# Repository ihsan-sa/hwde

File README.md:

# hwde

**An AI PCB engineer for KiCad and JLCPCB.** Printed circuit boards, designed
from a written brief.

This page is also a PDF with bigger pictures, the hwde showcase:
[hwde-showcase.pdf](docs/showcase/hwde-showcase.pdf). To install and run hwde,
see [Using hwde](docs/using-hwde.md).

You describe a board in plain words. hwde researches the parts, draws the
schematic, lays out and routes the board, checks it, and hands you the files a
factory needs to make it. A person reads the work and signs it off at each
stage before the next one starts.

*__lumina-carrier__ · 4 layers · 100 × 80 mm · 116 footprints · ordered,
fabricated. A carrier board for a stage-lighting fixture. hwde designed it, and
it was ordered from JLCPCB and made.*

## How a board is made

A board goes through five stages, and each stage ends with checks and a
person's sign-off.

*Figure 1. Each box is a stage, and each one writes a file the next one reads.*

A run starts from a brief, which can be a paragraph or a page. hwde first
researches the parts and picks an architecture, then chooses the real parts
and draws the schematic. Layout places the parts and routes the copper. The
checks run the electrical rules, the design rules and the circuit simulations,
and then the factory's own manufacturing rules on the exported Gerbers. What
comes out is the package: Gerbers, a bill of materials and a placement file
that JLCPCB can build and assemble from.

The work is split two ways. Subagents make the judgement calls, such as which
topology to use, how big a part must be, or whether a schematic is right, and
each one has a written contract that says what it may decide. Scripts do the
mechanical work, and they do it the same way every time. They drive KiCad, run
the routers and export the Gerbers. A script never makes a judgement, and an
agent never edits a board file by hand. Everything either of them makes is a
file in the board's own folder, so you can read it without hwde.

### What happens at the end of each stage

*Figure 2. A failed check or a refused sign-off goes to the fix loop, which
reworks the file and sends it round again.*

The checks that run depend on the stage, and each one writes its own report. A
pass only proves the checks that actually ran, which is why the reports are
kept one per check and not folded into a single verdict. When a check fails,
the fix loop reworks the file the stage made and the checks run again. When
they pass, a person still has to read the work and agree before the next stage
starts.

Every run also writes down what went wrong and why, with a date and a tag. The
next board reads those notes before it starts, so a mistake that cost one
board some time is not paid for again on the next.

## After the package

Three things can follow a finished package. A person can order the board,
/fwe can write its firmware, and /npie can plan how to bring it up.

*Figure 3. An order needs a person. Firmware and the bring-up plan have so far
run only in simulation.*

Ordering is deliberately hard to do by accident. JLCPCB has no public API for
its manufacturability review, so a person does that step in a browser. One
code path can place an order, and it takes 2-layer boards only. It refuses a
board whose files already record an order, and it will not run without a fresh
quote and a design that matches the one quoted. A person then has to type a
confirmation that names the board, the quantity and the total.

/fwe and /npie are two newer skills that take over where hwde stops. They
live in their own repositories, [ihsan-sa/fwe](https://github.com/ihsan-sa/fwe)
and [ihsan-sa/npie](https://github.com/ihsan-sa/npie). /fwe
writes firmware for a board, working from the board's own netlist to get the
pin map. /npie reads the same design and writes a staged bring-up procedure,
with pass and fail limits taken from the design, then runs it through one
driver layer that talks either to real instruments or to a simulated bench. So
far both have worked on one board, [the motor driver](#the-motor-driver), and
neither has touched hardware. The firmware builds, its unit tests pass on the
host, and it runs in the Renode emulator. The bring-up procedure has been run
once, against the simulated bench.

<!-- gallery:start - generated by docs/showcase/gallery.py from gallery.yaml and the boards repo; edit those, not this -->
## The boards

Twenty-three boards have reached a routed layout. They run from a linear
regulator with five parts to a three-phase motor driver.

| Board | What it is | Layers | Size (mm) | Where it stopped |
|---|---|--:|--:|---|
| stereo-class-d-amp | stereo class-D amplifier | 2 | 53.6 × 36.8 | made and measured, verification not passed |
| pd-trigger | USB-C PD bench trigger | 2 | 48 × 30 | ordered and made |
| lumina-carrier | lighting carrier, PoE-powered | 4 | 100 × 80 | ordered and made |
| rf-load-50ohm | 50 ohm / 200 W RF load at 13.56 MHz, fan-cooled, -40 dB tap | 2 | 60 × 60 | package ready |
| rp2040-mini | RP2040 dev board on the Pico footprint, USB-C | 2 | 21 × 51 | package ready |
| esp32c3-node | WiFi/BLE sensor node, LiPo | 2 | 26 × 38 | verification, findings open |
| lipo-boost | LiPo charger and 5 V boost | 2 | 53.9 × 38.8 | package ready |
| nfc-card | NFC business card | 2 | 88.9 × 50.8 | package ready |
| bldc-motor-driver | three-phase motor driver | 4 | 78 × 78 | package ready |
| pd-trigger-lite | small USB-C PD trigger | 2 | 25 × 15 | package ready |
| pd-trigger-lite-dip | the same, set by DIP switch | 2 | 25 × 21 | package ready |
| g0-sense | USB-C sensor node | 2 | 35.8 × 28.3 | package ready |
| bb-adc | single-channel ADC | 2 | 54.8 × 34.9 | package ready |
| bb-mcu | bare microcontroller board | 2 | 34.8 × 22.3 | package ready |
| bb-ldo | bare linear regulator | 2 | 34.7 × 34.7 | package ready |
| bb-amp | sensor amplifier chain | 2 | 48 × 28.3 | package ready |
| bb-buck | bare buck converter | 2 | 35 × 25 | package ready |
| rf-term-150w | 150 W RF dummy load head | 2 | 26 × 20 | package ready |
| rf-de-20m | 20 MHz Class E GaN stage | 4 | 120 × 80 | routing, findings open |
| sbuck-5v3a | 5 V / 3 A synchronous buck | 4 | 50 × 40 | package ready |
| usb-buck | USB device dev board | 4 | 50 × 40 | package ready |
| lumina-par | RGBW PAR daughter board | 4 | 100 × 80 | manufacturability, findings open |
| stm32-blinky | minimal STM32 dev board | 2 | 50 × 40 | package ready |

“Where it stopped” is the last stage the board reached, and it does not mean
the board is fit to release. Three boards were ordered from JLCPCB and made.
“Made and measured” means the board was also tested on a bench. “Package ready”
means every recorded check passed and the manufacturing package is built.
“Findings open” means a check failed and a person has yet to rule on it. Each
size is the bounding box of the board outline, and not every outline is a
rectangle.

### New boards

These boards were added after the rest of this chapter was written, so each
description is taken from the board's own requirements.

| | |
|---|---|
|  |  |
| __rf-load-50ohm__ · 2 layers · 60 × 60 mm · 21 footprints · package ready. A 50 ohm resistive RF load (dummy load) for 200 W continuous wave at 13.56 MHz, usable 1-30 MHz, for the owner's RF test system (it terminates the PCB-0023-A GaN inverter). | __rp2040-mini__ · 2 layers · 21 × 51 mm · 54 footprints · package ready. A general-purpose RP2040 microcontroller board that is a drop-in for the Raspberry Pi Pico (Raspberry Pi Ltd, 2021): same 21 x 51 mm outline, same 40-pin through-hole edge (as built: plain PTH, not castellated) with the Pico's pinout, same 3-pin SWD header position class (bottom edge, opposite USB). |

### The motor driver

*__bldc-motor-driver__ · 4 layers · 78 × 78 mm · 175 footprints · package
ready. A three-phase driver for brushless motors, running from 10 to 28 V. Six
N-channel MOSFETs make three half-bridges, a DRV8300 drives their gates, and an
STM32G431 runs the motor control. Each low-side leg has a 3 mΩ shunt read by an
INA240 current amplifier. The brief was a general spec and one frame of a video
showing someone else's demo board, so hwde wrote down every gap it had to fill
as a numbered assumption.*

The FETs are rated 60 V although the board runs at 28 V at most. The input TVS
diode clamps a surge at about 45 V, and every part on the motor supply is
chosen to survive that clamp, not just the working voltage. There is no fuse on
the board, and the notes call for a 20 A slow fuse in the supply lead.

*__bldc-motor-driver, top copper__ · F.Cu with net names. The three
half-bridges sit along the bottom edge, with phase A, B and C left to right,
each with its current amplifier below it. The board passes its checks with 390
written waivers, and the board's notes ask you to read them before you trust
it. Most cover stitching vias and the thin Kelvin and gate-return taps, which
the current-capacity check counts as power copper.*

This is the one board that /fwe and /npie have worked on. /fwe wrote the first
stage of its firmware, which spins the motor with six-step commutation. It
builds with warnings treated as errors, its unit tests pass on the host, and it
runs on an emulated STM32G431 in Renode. /npie wrote a bring-up procedure for
the board and ran it once against a simulated bench, where it passed. Neither
result says anything about real hardware, because the board has not been made.

### The amplifier

*__stereo-class-d-amp__ · 2 layers · 53.6 × 36.8 mm · 44 footprints · made and
measured, verification not passed. A stereo class-D amplifier that runs from a
single 12 V supply and drives 4 to 8 Ω speakers. Each output has a 10 µH LC
filter. The brief asked hwde to reproduce a published reference design, so the
two can be compared.*

The brief named the TPA3116D2, but hwde used the TPA3118D2 instead. The 3116
only comes with its thermal pad on top, which needs a heatsink bolted on. The
3118 has the pad underneath and sheds its heat into the board, so hwde kept a
25 by 25 mm ground area clear around it on both layers. That area is why the
board is bigger than the 44 by 34 mm reference.

*__stereo-class-d-amp, top copper__ · F.Cu with net names. The amplifier sits
in the middle of a solid ground pour, with the left channel's filter below it
and the right channel's above. The input connector is on the left edge and the
speaker pads are on the right.*

Ten assembled boards were ordered from JLCPCB on 30 September 2026, and one was
wired up and measured on the bench on 13 October. From 12 V into 6 Ω speakers,
one channel gave 10.9 W at 0.37% THD, and at 4.1 W a channel the board
delivered about 90% of its supply power to the speakers. It was ordered before
its verification checks passed, with eight waivers unsigned, and nobody has yet
measured the chip's temperature under load.

### A card, a sensor node and a battery board

These three were designed unattended on the same morning. The owner told hwde
to decide for itself, so hwde signed off its own stages and wrote down each
call it made, with the reason.

*__nfc-card__ · 2 layers · 88.9 × 50.8 mm · 19 footprints · package ready. A
business card you tap with a phone. The phone reads a web address from the NFC
tag and opens it, and while the phone is near, the tag takes power from its
field and lights a pattern of LEDs. There is no battery and no microcontroller.
The antenna is a coil printed around the edge of a 0.8 mm board, thin enough to
carry in a wallet.*

| | |
|---|---|
|  |  |
| __esp32c3-node__ · 2 layers · 26 × 38 mm · 41 footprints · verification, findings open. A small WiFi and Bluetooth sensor node built around an ESP32-C3 module. USB-C powers it and also flashes it, through the chip's own USB, so there is no USB-serial bridge. It charges a single LiPo cell and keeps running with or without one, and a BME280 and a Qwiic connector share one I²C bus. | __lipo-boost__ · 2 layers · 53.9 × 38.8 mm · 33 footprints · package ready. It charges a single LiPo cell from USB and makes 5 V at 1 A on a USB-A socket from the cell. While USB is plugged in, the output keeps running from USB as the cell charges. The brief asked for a board in the class of the PowerBoost 1000C, designed from the datasheets rather than copied. |

### The small PD triggers

| | |
|---|---|
|  |  |
| __pd-trigger-lite__ · 2 layers · 25 × 15 mm · 15 footprints · package ready. Plug in a USB-C charger and the board asks it for 9, 12, 15 or 20 V, at up to 3 A, and passes it to two output holes. One solder link picks the voltage. hwde chose the CH224A over the CH224K the brief named, because its sense pin takes the bus voltage directly. That removes a dropper resistor, a sense resistor and the pull-ups. | __pd-trigger-lite-dip__ · 2 layers · 25 × 21 mm · 13 footprints · package ready. The same board with a five-way DIP switch instead of the solder links, which adds 5 V to the choices. You set exactly one switch before you plug it in. The board grew from 15 to 21 mm to make room for the switch. |

Both are smaller versions of pd-trigger, the bench tool that was ordered and
made.

### Ordered and fabricated

lumina-carrier, the board at the start, is the carrier for a stage-lighting
fixture. It takes power over Ethernet through a PD controller and a 100 V buck,
and it has an expansion connector that a fixture-specific daughter board plugs
into. The connector's pinout is frozen, because another board depends on it.
The amplifier was ordered too, and the third board that was ordered is a bench
tool.

*__pd-trigger__ · 2 layers · 48 × 30 mm · 30 footprints · ordered and made. A
USB-C Power Delivery sink asks a charger for 5, 9, 12, 15 or 20 V, and you pick
which on the board. The rail comes out on a screw terminal rated for 5 A. The
board converts nothing and just passes the rail through.*

### Power and RF

| | |
|---|---|
|  |  |
| __sbuck-5v3a__ · 4 layers · 50 × 40 mm · 44 footprints · package ready. A synchronous buck that takes 7–18 V in and holds 5.0 V ±2% at 3 A out. It is an open-frame power module. | __rf-term-150w__ · 2 layers · 26 × 20 mm · 6 footprints · package ready. A 50 Ω, 150 W dummy load head for DC to 25 MHz. The element bolts to a heatsink you supply, so the board is only the RF launch and the mounting. It looks almost bare because none of its six footprints has a 3D model, so the connector and the element are not drawn. |

*__rf-de-20m__ · 4 layers · 120 × 80 mm · 80 footprints · routing, findings
open. A 20 MHz Class E RF power stage that puts 200 W into 50 Ω from a 40 V
bus. A GaN gate driver buffers the PWM drive from an SMA input, and one eGaN
FET switches. A resonant tank and an L-match turn the 4.6 Ω load line into 50 Ω
at the output SMA. The owner fixed the topology and the two core parts after a
costed trade study, and hwde did the rest.*

### Lighting

*__lumina-par__ · 4 layers · 100 × 80 mm · 158 footprints · manufacturability,
findings open. The RGBW PAR daughter board that stacks on lumina-carrier. It
takes the carrier's frozen connector as given. Its power budget depends on the
power-over-Ethernet class the fixture is granted, so hwde worked it out again
here. The silkscreen warns that the board floats at the power-over-Ethernet
potential, because an earthed probe breaks the fixture's power negotiation.*

| | |
|---|---|
|  |  |
| __lumina-par, straight down__ · top-down view. The same board from straight above, so the routing shows. | __lumina-carrier, underneath__ · bottom view. Every part on the carrier is on the top side, so the back carries routing and vias and nothing else. |

### Microcontroller boards

*__g0-sense__ · 2 layers · 35.8 × 28.3 mm · 30 footprints · package ready. A
temperature and humidity node that runs off USB-C. An LDO makes 3.3 V from the
5 V supply, and an STM32G030 reads a Sensirion SHT4x over I²C. The same bus
comes out on a Qwiic connector, the readings go out on a UART header, and you
program it over SWD. hwde designed this one from end to end in a single
unattended run.*

| | |
|---|---|
|  |  |
| __usb-buck__ · 4 layers · 50 × 40 mm · 28 footprints · package ready. An STM32F103 board that talks USB at full speed. The Micro-B socket carries both power and data, and there is an LED, a button and an SWD header. | __stm32-blinky__ · 2 layers · 50 × 40 mm · 20 footprints · package ready. The simplest useful board here: an STM32F103, an 8 MHz crystal, one LED, an LDO and an SWD header. |

### Building blocks

These five boards each carry a single block and nothing else. They are meant to
be studied and measured on a bench, so they leave out protection, filtering,
indicators and spare rails on purpose.

| | |
|---|---|
|  |  |
| __bb-buck__ · 2 layers · 35 × 25 mm · 20 footprints · package ready. 18–30 V in and 5 V at 2 A out, on a screw terminal. It carries the converter and exactly what its datasheet requires. | __bb-ldo__ · 2 layers · 34.7 × 34.7 mm · 5 footprints · package ready. 5 V in and 3.3 V at 500 mA out. It stays in regulation in still air on the board's own copper. |
|  |  |
| __bb-mcu__ · 2 layers · 34.8 × 22.3 mm · 14 footprints · package ready. One MCU with a 3.3 V rail coming in, its debug header and four GPIO. There is no regulator and no second rail. | __bb-adc__ · 2 layers · 54.8 × 34.9 mm · 25 footprints · package ready. 0–5 V in on a screw terminal and 12 bits at up to 10 kSa/s out on a header. It gives up speed for DC accuracy. |
|  | |
| __bb-amp__ · 2 layers · 48 × 28.3 mm · 14 footprints · package ready. A 0–20 mV bridge signal in and 0–3.3 V out, from DC to 1 kHz. | |

Two more boards stopped before layout and have no PCB to show: lumina-strobe
(LUMINA strobe daughter board) and buck-5v3a (12 V to 5 V / 3 A synchronous
buck). They are in the boards repository at the stage they reached.
<!-- gallery:end -->

## What it can and cannot do yet

hwde is an engineering assistant. It does not release a board on its own, and
a person signs off at every stage.

**What holds**

- Every board in the table went from a written brief to a routed layout, among
  them a 4-layer 200 W RF stage and a 4-layer motor driver.
- The ones marked ordered were made by JLCPCB, and their files record the
  order numbers.
- Every check is a script, and the findings are kept per check rather than as
  a single verdict.
- Everything a run produces is a file in that board's folder, and you can read
  it without hwde.

**What does not**

- JLCPCB's manufacturability review has no public API, so a person still does
  that step in a browser.
- The electrical and thermal checks are engineering screens, and each states
  its own accuracy. None of them is a certification, and nothing here is
  certified for mains, medical, automotive or aerospace use.
- The firmware and the bring-up procedure have only run in simulation. The
  amplifier, which has no firmware, was measured on a real bench by hand, but
  no board has been brought up with them yet.

---

Board facts come from each board's own files in the boards repository
(`.kicad_pcb`, `state.json` and its notes), and the gallery above is
regenerated from them whenever a board is added or changed. How that works,
and how to rebuild the pictures and the PDF, is in
[docs/showcase](docs/showcase/README.md).

To install and run hwde, call it from another agent, or find which document
answers which question, see [Using hwde](docs/using-hwde.md).

## License

MIT - see [LICENSE](LICENSE). Vendor datasheets, component 3D models and
footprints pulled from LCSC/EasyEDA are third-party material, not under MIT -
see [NOTICE](NOTICE).

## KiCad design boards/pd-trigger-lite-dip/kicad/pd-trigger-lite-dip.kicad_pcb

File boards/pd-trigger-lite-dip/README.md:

# pd-trigger-lite-dip

A 25 x 21 mm, 2-layer USB-C PD trigger. Plug in a PD charger and it passes VBUS straight to two
2.54 mm output holes at 5, 9, 12, 15 or 20 V (3 A max). The voltage is picked with a 5-position
DIP switch: exactly one switch ON, set before plugging in. It is pd-trigger-lite with the solder
links replaced by the switch. Controller: WCH CH224A. Full owner guide, with the switch table:
`fab/pd-trigger-lite-dip-guide.pdf`.

| Switch ON (others OFF) | 1 | 2 | 3 | 4 | 5 |
|---|---|---|---|---|---|
| Output | 5 V | 9 V | 12 V | 15 V | 20 V |

## Files

| Path | What it is |
|---|---|
| `fab/pd-trigger-lite-dip-guide.pdf` | Owner guide: what it does, schematic, switch settings, BOM, cost, JLC ordering |
| `fab/pd-trigger-lite-dip_gerbers.zip` | Gerbers + drill for JLCPCB |
| `fab/BOM.csv` | JLC assembly BOM (Comment, Designator, Footprint, LCSC Part #) |
| `fab/CPL.csv` | JLC placement file (Designator, Mid X, Mid Y, Layer, Rotation) |
| `fab/prebuy.csv` | Extended parts you may need to pre-buy at JLC, with quantities for 5 boards |
| `fab/BOM-full.csv` | BOM of record incl. the unassembled output holes (J2) |
| `fab/quote.json` | Estimated JLC quote, qty 5 with assembly |
| `kicad/` | KiCad 10 project; the schematic is generated by `kicad/gen/root.py` |
| `reports/` | ERC/DRC/verify/DFM gate reports, schematic PDF, renders, guide source |
| `architecture/`, `requirements.md`, `log/` | Design decisions and the run journal |

## Estimated cost, 5 boards assembled at JLC (2026-09-24)

| Item | USD |
|---|---|
| PCB, 5 pcs, 2 layers, 25 x 21 mm, 1.6 mm, HASL | 2.00 |
| Economic PCBA setup | 8.00 |
| Stencil | 8.00 |
| Extended-part fees: CH224A, USB-C receptacle, DIP switch (3 x 3.00) | 9.00 |
| Solder joints (49 x 5 x 0.0017) | 0.42 |
| Parts, 5 boards (about 1.09 per board, LCSC unit prices; the switch is 0.53) | 5.44 |
| **Total before shipping** | **about 33** |

Assumptions: prices from the hwde price table (`reference/jlc_pricing.yaml`, verified 2026-07-24)
and LCSC unit prices pulled 2026-09-24. These are estimates: live JLC bare-PCB prices have run
1.9-3.1x above that table, so allow roughly 33-40 USD. Shipping is extra and region-dependent
(about 2-20 USD depending on carrier). The JLC cart is the only real quote. Nothing has been ordered.

## You may need to pre-buy these at JLC

JLC's BOM review may show an Extended part as idle stock: unselected, at quantity 0, until you buy
it into your JLC parts inventory. JLC's public parts search can't tell idle stock from stock that
assembles straight away, so every Extended part is listed. If one comes up unselected, buy it from
the BOM review page, then select it.

| LCSC | Part | Ref | Qty for 5 boards |
|---|---|---|---|
| C2798175 | USB-C receptacle 6P (TYPE-C-6M-001) | J1 | 5 |
| C7421518 | DIP switch 5P, 1.27 mm (1.27-5P TPPT) | SW1 | 5 |
| C42459160 | CH224A PD sink controller | U1 | 5 |

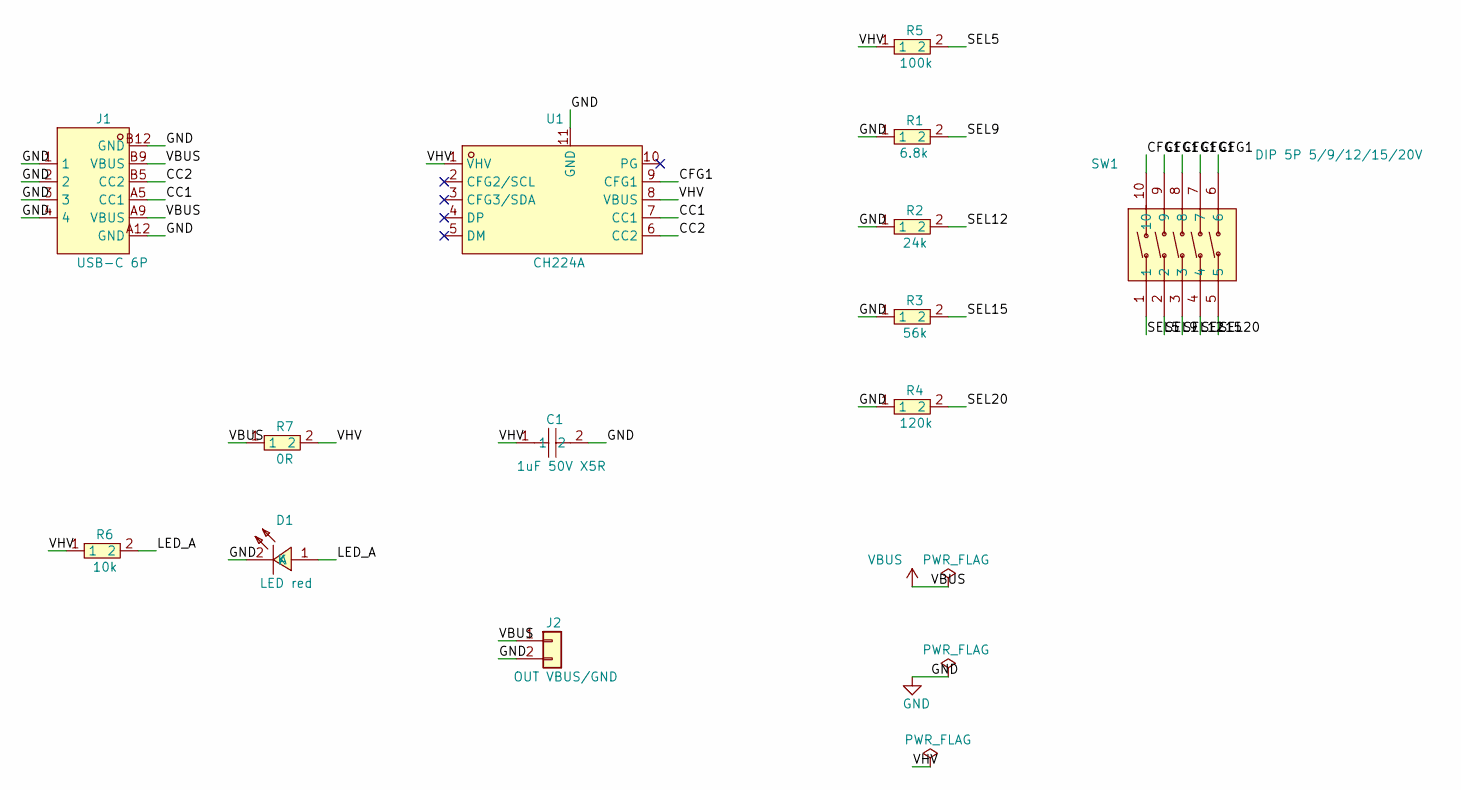
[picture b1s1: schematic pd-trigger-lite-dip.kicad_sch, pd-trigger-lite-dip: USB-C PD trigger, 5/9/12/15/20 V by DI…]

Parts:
C1: 1uF 50V X5R; C0603; LCSC C15849
D1: LED red; LED-SMD_L1.6-W0.8-R-RD; LCSC C2286
J1: USB-C 6P; USB-C-SMD_918-418K2023S40006; LCSC C2798175
J2: OUT VBUS/GND; OUT_2P_P2.54_D1.1
R1: 6.8k; R0603; LCSC C23212
R2: 24k; R0603; LCSC C23352
R3: 56k; R0603; LCSC C23206
R4: 120k; R0603; LCSC C25808
R5: 100k; R0603; LCSC C25803
R6: 10k; R0603; LCSC C25804
R7: 0R; R0603; LCSC C21189
SW1: DIP 5P 5/9/12/15/20V; SW-SMD_5P-P1.27_1.27-5P; LCSC C7421518
U1: CH224A; ESSOP-10_L4.9-W3.9-P1.0-LS6.0-TL-EP; LCSC C42459160

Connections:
/CC1: J1.A5 (CC1), U1.7 (CC1)
/CC2: J1.B5 (CC2), U1.6 (CC2)
/CFG1: SW1.6, SW1.7, SW1.8, SW1.9, SW1.10, U1.9 (CFG1)
/LED_A: D1.1 (A), R6.2
/SEL5: R5.2, SW1.1
/SEL9: R1.2, SW1.2
/SEL12: R2.2, SW1.3
/SEL15: R3.2, SW1.4
/SEL20: R4.2, SW1.5
/VHV: C1.1, R5.1, R6.1, R7.2, U1.1 (VHV), U1.8 (VBUS)
GND: C1.2, D1.2 (K), J1.1, J1.2, J1.3, J1.4, J1.A12 (GND), J1.B12 (GND), J2.2, R1.1, R2.1, R3.1, R4.1, U1.11 (GND)
VBUS: J1.A9 (VBUS), J1.B9 (VBUS), J2.1, R7.1

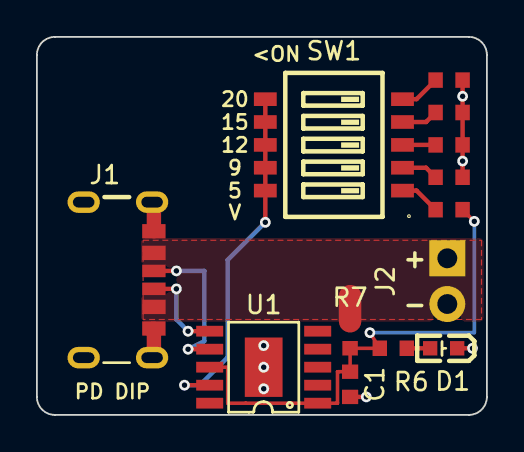
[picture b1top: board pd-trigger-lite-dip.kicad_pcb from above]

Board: 2 copper layers, 25.0 x 21.0 mm, 13 parts (0 on the bottom side), 12 nets.

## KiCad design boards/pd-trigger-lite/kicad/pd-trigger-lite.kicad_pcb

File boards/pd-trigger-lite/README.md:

# pd-trigger-lite

A 25 x 15 mm, 2-layer USB-C PD trigger. Plug in a PD charger and it passes VBUS straight to two
2.54 mm output holes at 9, 12, 15 or 20 V (3 A max). The voltage is set by one 0603 link; it ships
at 12 V. Controller: WCH CH224A in single-resistor mode. Full owner guide: `fab/pd-trigger-lite-guide.pdf`.

## Files

| Path | What it is |
|---|---|
| `fab/pd-trigger-lite-guide.pdf` | Owner guide: what it does, schematic, voltage setting, BOM, cost, JLC ordering |
| `fab/pd-trigger-lite_gerbers.zip` | Gerbers + drill for JLCPCB |
| `fab/BOM.csv` | JLC assembly BOM (Comment, Designator, Footprint, LCSC Part #) |
| `fab/CPL.csv` | JLC placement file (Designator, Mid X, Mid Y, Layer, Rotation) |
| `fab/BOM-full.csv` | BOM of record incl. the unassembled links (JP1-3) and output holes (J2) |
| `fab/quote.json` | Estimated JLC quote, qty 5 with assembly |
| `kicad/` | KiCad 10 project; the schematic is generated by `kicad/gen/root.py` |
| `reports/` | ERC/DRC/verify/DFM gate reports, schematic PDF, renders, reviews |
| `architecture/`, `requirements.md`, `log/` | Design decisions and the run journal |

## Estimated cost, 5 boards assembled at JLC (2026-09-24)

| Item | USD |
|---|---|
| PCB, 5 pcs, 2 layers, 25 x 15 mm, 1.6 mm, HASL | 2.00 |
| Economic PCBA setup | 8.00 |
| Stencil | 8.00 |
| Extended-part fees: CH224A, USB-C receptacle (2 x 3.00) | 6.00 |
| Solder joints (39 x 5 x 0.0017) | 0.33 |
| Parts, 5 boards (about 0.56 per board, LCSC unit prices) | 2.78 |
| **Total before shipping** | **about 27** |

Assumptions: prices from the hwde price table (`reference/jlc_pricing.yaml`, verified 2026-07-24)
and LCSC unit prices pulled 2026-09-24. These are estimates: live JLC bare-PCB prices have run
1.9-3.1x above that table, so allow roughly 27-35 USD. Shipping is extra and region-dependent
(about 2-20 USD depending on carrier). The JLC cart is the only real quote. Nothing has been ordered.

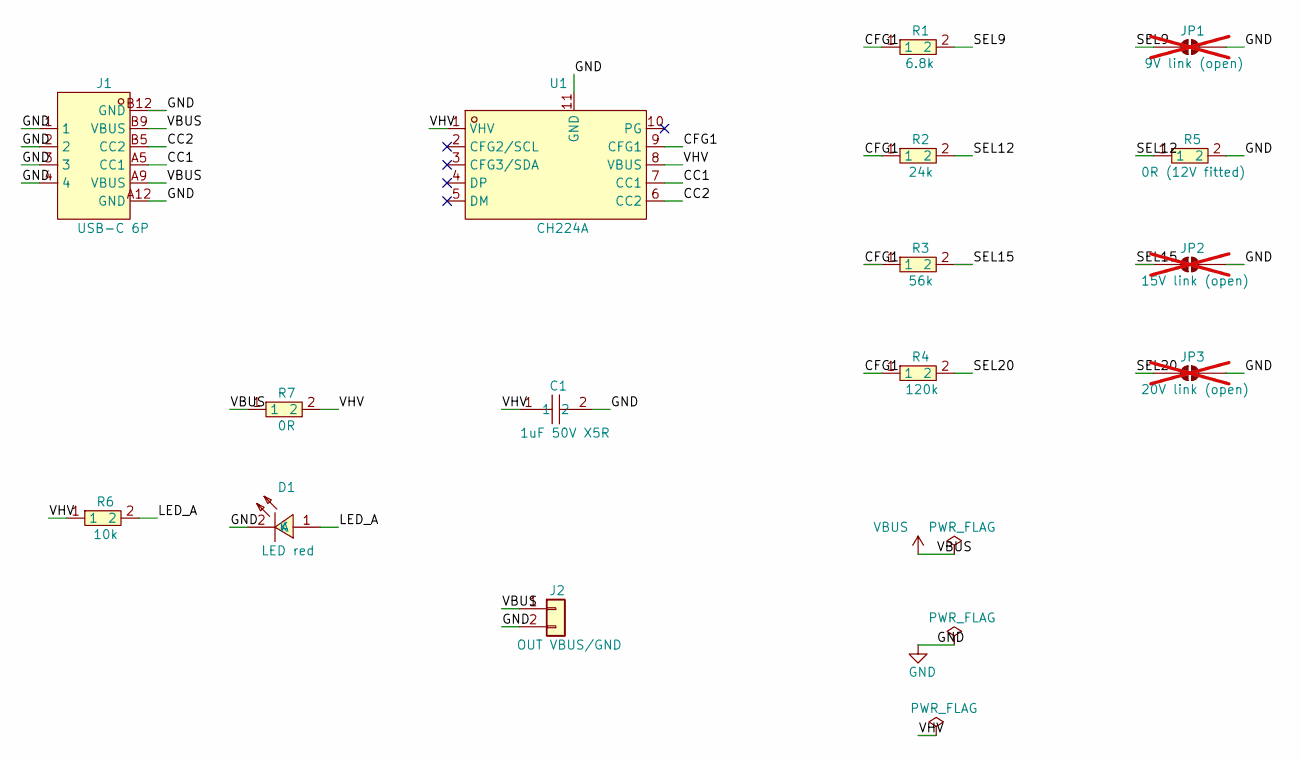
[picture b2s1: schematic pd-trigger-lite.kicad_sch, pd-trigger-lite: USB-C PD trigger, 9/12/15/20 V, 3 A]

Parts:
C1: 1uF 50V X5R; C0603; LCSC C15849
D1: LED red; LED-SMD_L1.6-W0.8-R-RD; LCSC C2286
J1: USB-C 6P; USB-C-SMD_918-418K2023S40006; LCSC C2798175
J2: OUT VBUS/GND; OUT_2P_P2.54_D1.1
JP1: 9V link (open); R0603; not fitted
JP2: 15V link (open); R0603; not fitted
JP3: 20V link (open); R0603; not fitted
R1: 6.8k; R0603; LCSC C23212
R2: 24k; R0603; LCSC C23352
R3: 56k; R0603; LCSC C23206
R4: 120k; R0603; LCSC C25808
R5: 0R (12V fitted); R0603; LCSC C21189
R6: 10k; R0603; LCSC C25804
R7: 0R; R0603; LCSC C21189
U1: CH224A; ESSOP-10_L4.9-W3.9-P1.0-LS6.0-TL-EP; LCSC C42459160

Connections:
/CC1: J1.A5 (CC1), U1.7 (CC1)
/CC2: J1.B5 (CC2), U1.6 (CC2)
/CFG1: R1.1, R2.1, R3.1, R4.1, U1.9 (CFG1)
/LED_A: D1.1 (A), R6.2
/SEL9: JP1.1 (A), R1.2
/SEL12: R2.2, R5.1
/SEL15: JP2.1 (A), R3.2
/SEL20: JP3.1 (A), R4.2
/VHV: C1.1, R6.1, R7.2, U1.1 (VHV), U1.8 (VBUS)
GND: C1.2, D1.2 (K), J1.1, J1.2, J1.3, J1.4, J1.A12 (GND), J1.B12 (GND), J2.2, JP1.2 (B), JP2.2 (B), JP3.2 (B), R5.2, U1.11 (GND)
VBUS: J1.A9 (VBUS), J1.B9 (VBUS), J2.1, R7.1

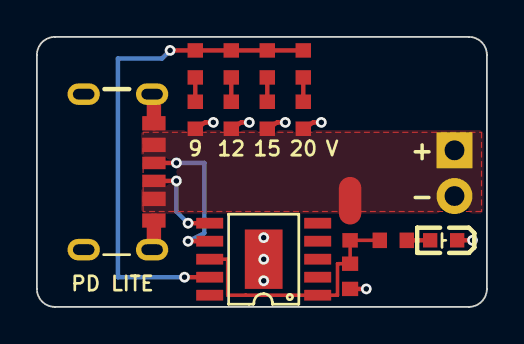
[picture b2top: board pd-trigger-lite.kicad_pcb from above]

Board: 2 copper layers, 25.0 x 15.0 mm, 15 parts (0 on the bottom side), 11 nets.

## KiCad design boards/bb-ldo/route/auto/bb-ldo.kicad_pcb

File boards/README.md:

# ai-ee3 boards

Board workspaces designed by the `/ai-ee` skill (github.com/ihsan-sa/ai-ee).
This repo is a derived view of the `boards/` subtree of the private build repo
`ai-ee3` (the canonical source) - synced via `git subtree split --prefix=boards`.

| Board | Class | State |
|---|---|---|
| stm32-blinky | 2L STM32 blinky (v1 hardening run a) | order-ready package |
| usb-buck | 4L USB-FS + buck (v1 hardening run b) | order-ready package |
| pd-trigger | USB-C PD trigger (novel, run c) | ORDERED (JLC, 2026-07) |
| lumina-carrier | 4L PoE ESP32 carrier | ORDERED (JLC web, 2026-07); rework R1 before power-on |
| lumina-par | PoE RGB+W par light daughter | in design (P8) |
| lumina-strobe | PoE strobe daughter | in design (P4) |
| sbuck-5v3a | 4L 12V -> 5V/3A synchronous buck (v2 live run) | order-ready package (P10) |
| buck-5v3a | first attempt at the same buck brief | **SUPERSEDED by sbuck-5v3a**, closed at P3 - do not resume |
| rf-term-150w | 150 W RF terminator, tuned launch (v2 live run) | P9, order-ready package |
| rf-de-20m | 20 m receive down-converter (external intake) | P9, constrained prototype - see `fab/README.md` |
| xhp-driver | high-power LED driver | brief only (P0) |

Per-board layout: `brief/` `research/` `architecture/` `parts/` `lib/` `kicad/`
`routing/` `reports/` `fab/` `log/` + `state.json` (phase, gates, decisions,
human holds). `fab/` contains the order-ready JLCPCB package (gerbers, BOM, CPL,
quotes, order/tracking records).

Private: fab records carry order numbers and ship-region metadata.

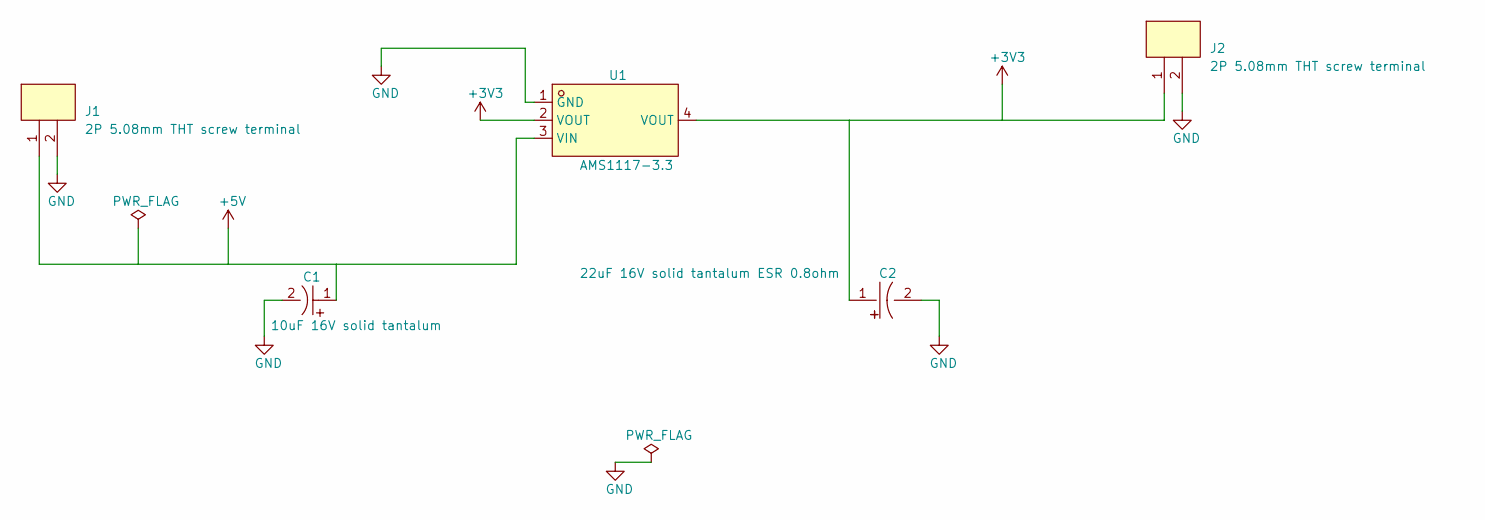
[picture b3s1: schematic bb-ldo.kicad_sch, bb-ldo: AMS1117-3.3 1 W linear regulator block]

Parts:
C1: 10uF 16V solid tantalum; CAP-SMD_L3.2-W1.6-RD-C7171; LCSC C7171
C2: 22uF 16V solid tantalum ESR 0.8ohm; CAP-SMD_L7.3-W4.3; LCSC C215872
J1, J2: 2P 5.08mm THT screw terminal; CONN-TH_2P-P5.00_WJ500V-5.08-2P; LCSC C8465
U1: AMS1117-3.3; SOT-223-3_L6.5-W3.4-P2.30-LS7.0-BR; LCSC C6186

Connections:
+3V3: C2.1, J2.1, U1.2 (VOUT), U1.4 (VOUT)
+5V: C1.1, J1.1, U1.3 (VIN)
GND: C1.2, C2.2, J1.2, J2.2, U1.1 (GND)

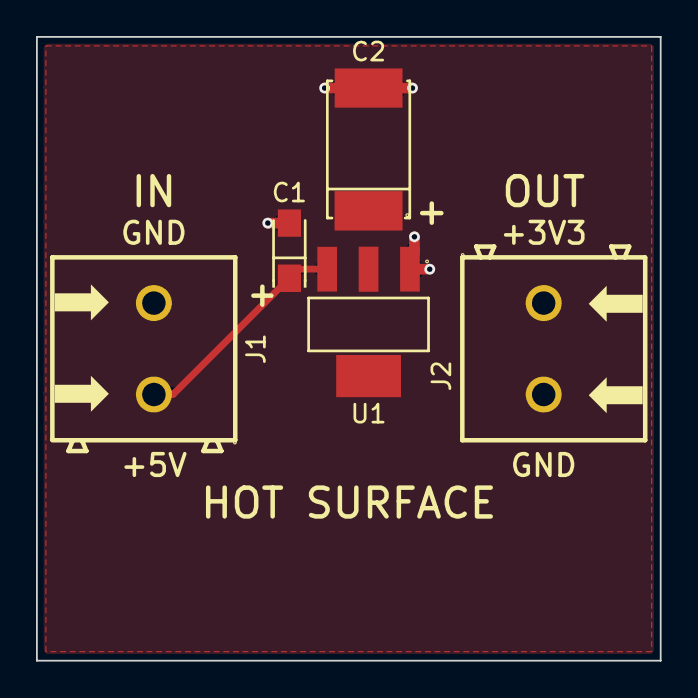
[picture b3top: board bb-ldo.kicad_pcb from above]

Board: 2 copper layers, 34.7 x 34.7 mm, 5 parts (0 on the bottom side), 3 nets.

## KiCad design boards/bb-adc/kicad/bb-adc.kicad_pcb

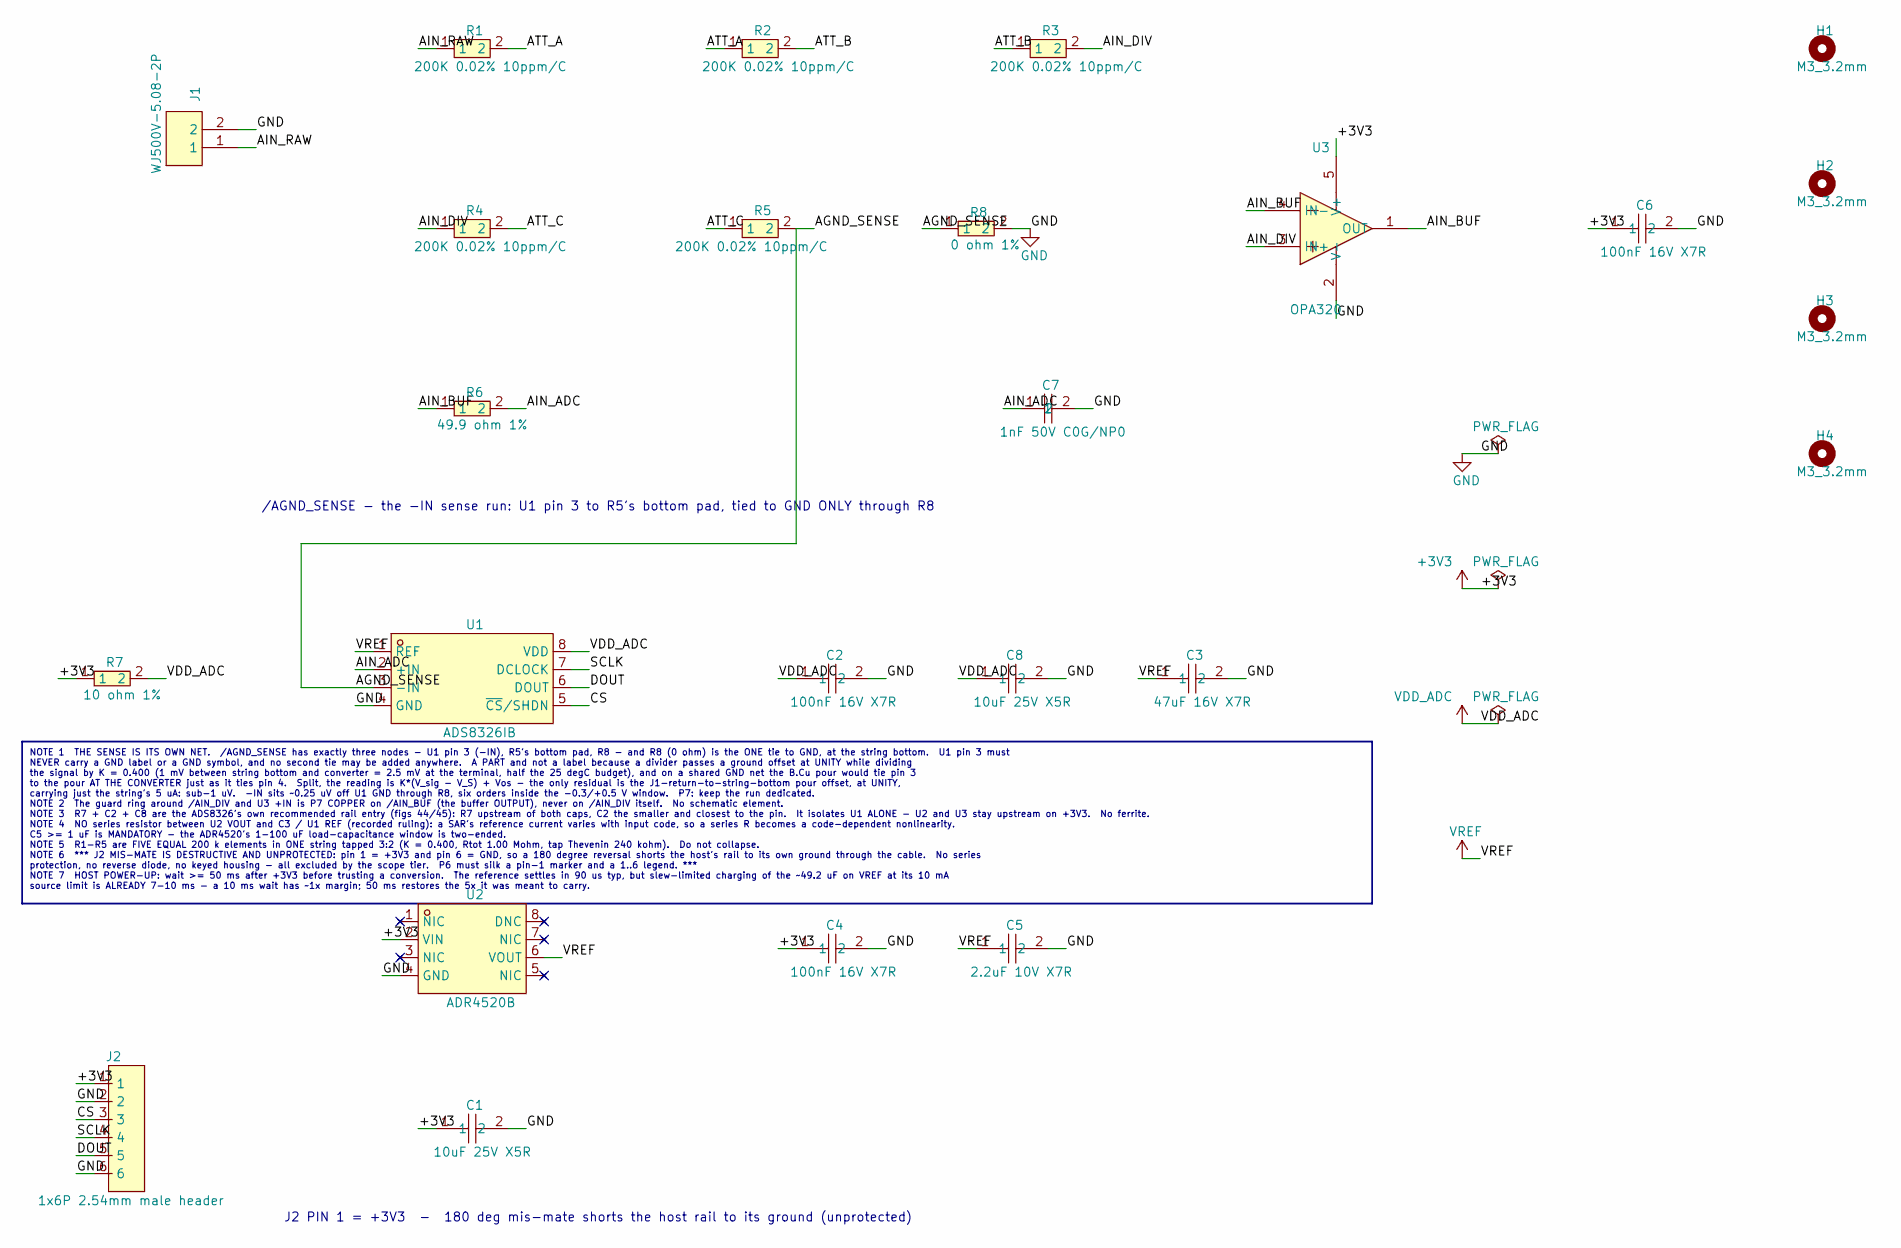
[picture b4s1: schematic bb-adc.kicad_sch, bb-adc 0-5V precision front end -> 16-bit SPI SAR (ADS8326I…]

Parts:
C1, C8: 10uF 25V X5R; C0805; LCSC C15850
C2, C4, C6: 100nF 16V X7R; C0402; LCSC C1525
C3: 47uF 16V X7R; C1210; LCSC C5440143
C5: 2.2uF 10V X7R; C0603; LCSC C513691
C7: 1nF 50V C0G/NP0; C0603; LCSC C106246
H1, H2, H3, H4: M3_3.2mm; MountingHole_3.2mm_M3
J1: WJ500V-5.08-2P; CONN-TH_2P-P5.00_WJ500V-5.08-2P; LCSC C8465
J2: 1x6P 2.54mm male header; HDR-TH_6P-P2.54-V-M-1; LCSC C37208
R1, R2, R3, R4, R5: 200K 0.02% 10ppm/C; R0805; LCSC C23067436
R6: 49.9 ohm 1%; R0603; LCSC C23185
R7: 10 ohm 1%; R0603; LCSC C22859
R8: 0 ohm 1%; R0603; LCSC C21189
U1: ADS8326IB; VSSOP-8_L3.0-W3.0-P0.65-LS5.0-BL; LCSC C544731
U2: ADR4520B; SOIC-8_L5.0-W4.0-P1.27-LS6.0-BL; LCSC C579305
U3: OPA320; SOT-23-5_L3.0-W1.7-P0.95-LS2.8-BR; LCSC C92494

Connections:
+3V3: C1.1, C4.1, C6.1, J2.1, R7.1, U2.2 (VIN), U3.5 (V+)
/AGND_SENSE: R5.2, R8.1, U1.3 (-IN)
/AIN_ADC: C7.1, R6.2, U1.2 (+IN)
/AIN_BUF: R6.1, U3.1 (OUT), U3.4 (IN-)
/AIN_DIV: R3.2, R4.1, U3.3 (IN+)
/AIN_RAW: J1.1, R1.1
/ATT_A: R1.2, R2.1
/ATT_B: R2.2, R3.1
/ATT_C: R4.2, R5.1
/CS: J2.3, U1.5 (~CS/SHDN)
/DOUT: J2.5, U1.6 (DOUT)
/SCLK: J2.4, U1.7 (DCLOCK)
GND: C1.2, C2.2, C3.2, C4.2, C5.2, C6.2, C7.2, C8.2, J1.2, J2.2, J2.6, R8.2, U1.4 (GND), U2.4 (GND), U3.2 (V-)
VDD_ADC: C2.1, C8.1, R7.2, U1.8 (VDD)
VREF: C3.1, C5.1, U1.1 (REF), U2.6 (VOUT)

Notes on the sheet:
/AGND_SENSE - the -IN sense run: U1 pin 3 to R5's bottom pad, tied to GND ONLY through R8
J2 PIN 1 = +3V3 - 180 deg mis-mate shorts the host rail to its ground (unprotected)
NOTE 1 THE SENSE IS ITS OWN NET. /AGND_SENSE has exactly three nodes - U1 pin 3 (-IN), R5's bottom pad, R8 - and R8 (0 ohm) is the ONE tie to GND, at the string bottom. U1 pin 3 must NEVER carry a GND label or a GND symbol, and no second tie may be added anywhere. A PART and not a label because a d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

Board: 2 copper layers, 25 parts (0 on the bottom side), 15 nets, no tracks yet.

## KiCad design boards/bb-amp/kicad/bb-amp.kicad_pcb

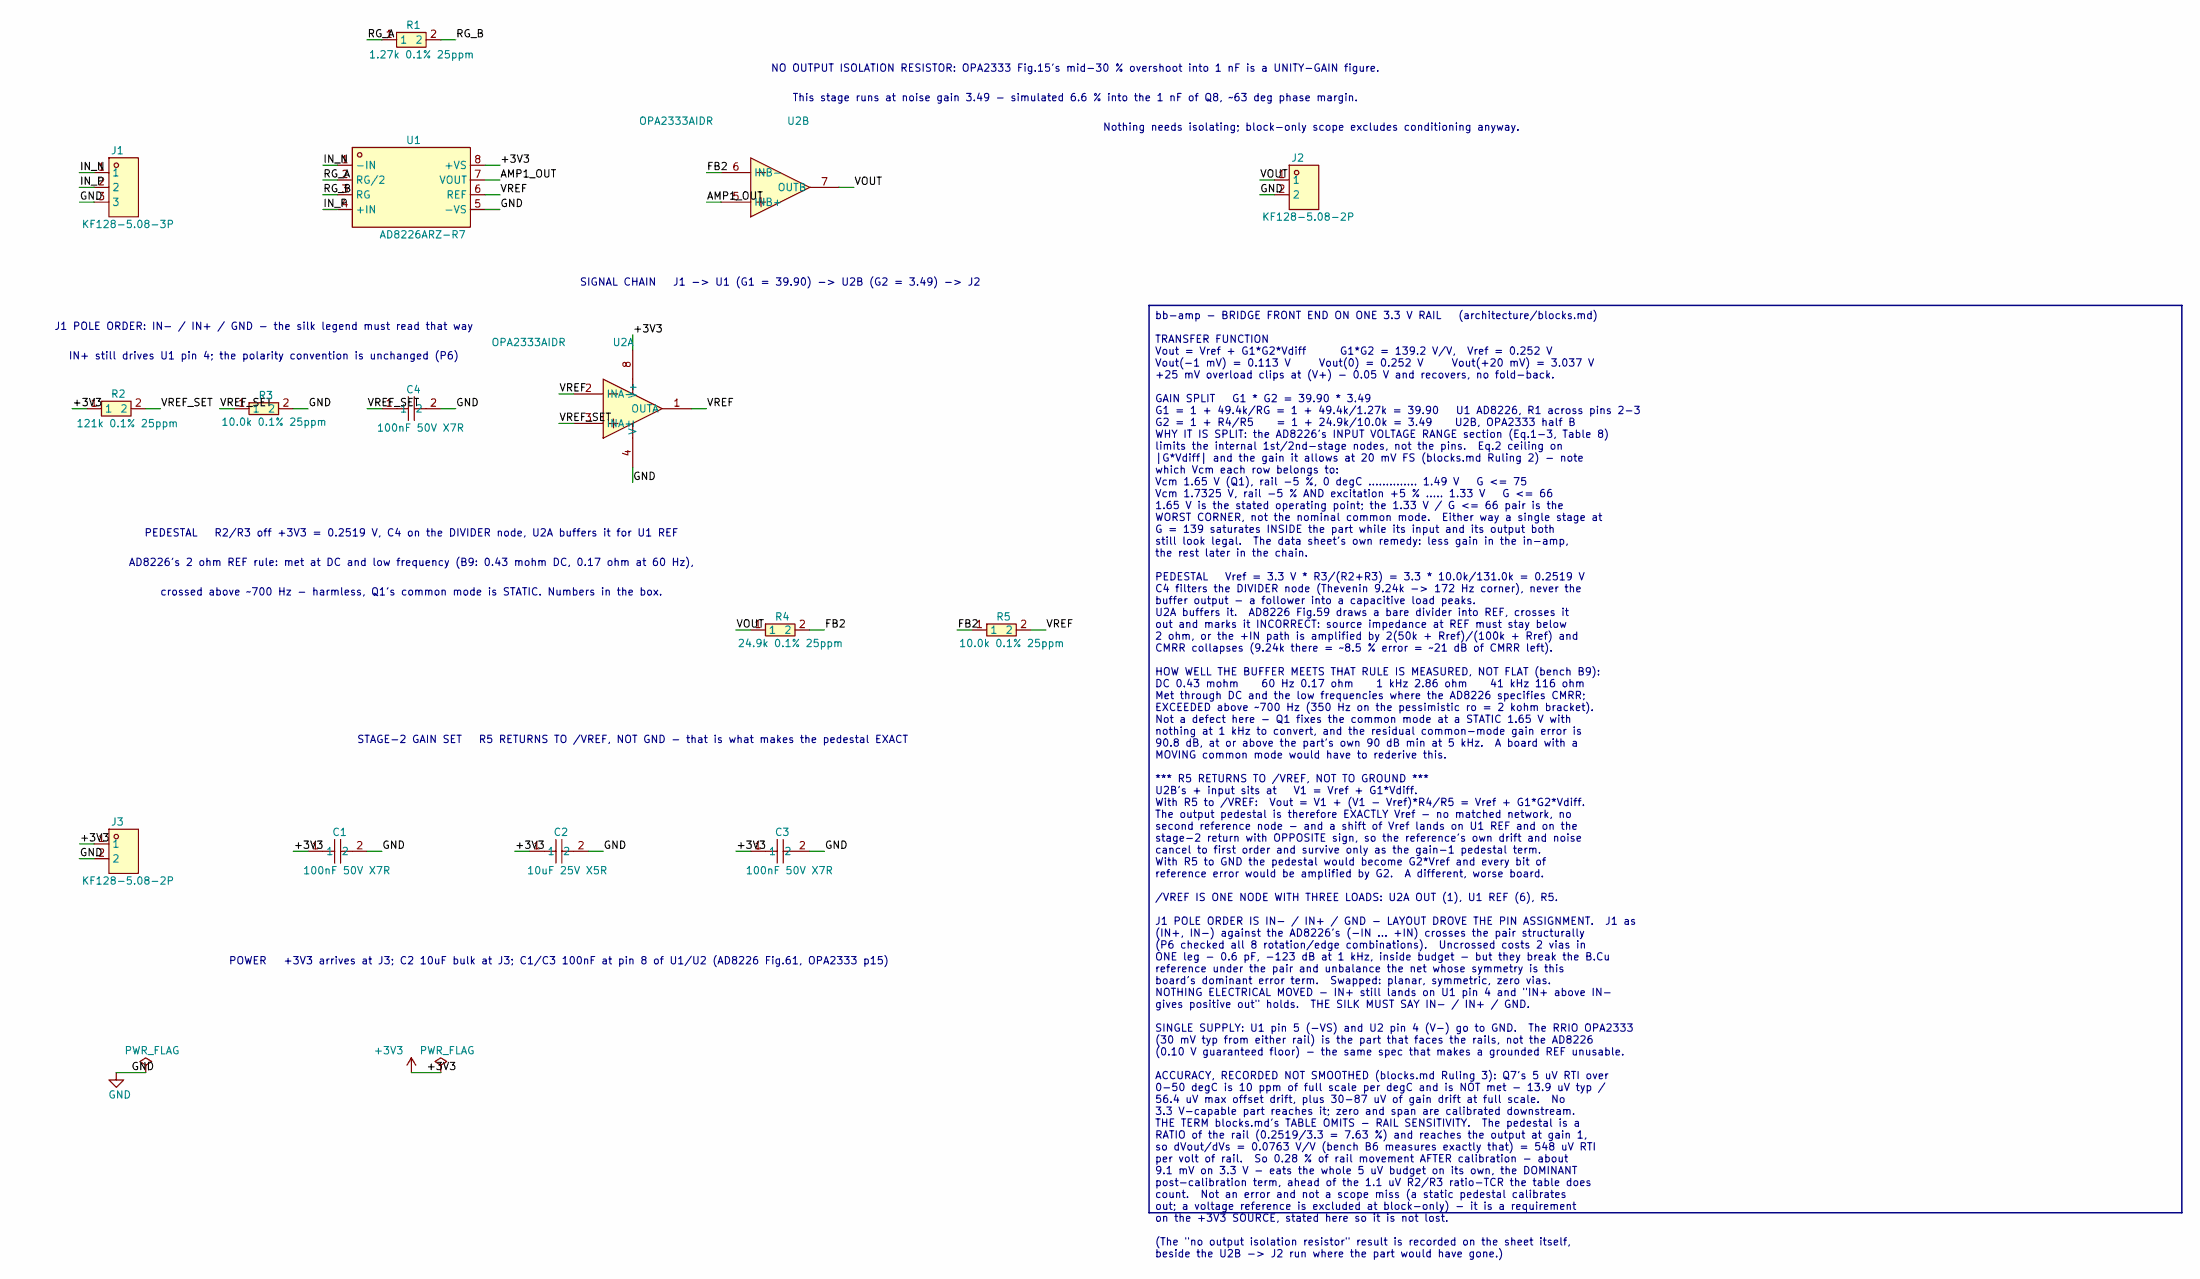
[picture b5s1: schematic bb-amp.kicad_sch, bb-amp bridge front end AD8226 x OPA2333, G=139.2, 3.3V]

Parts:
C1, C3, C4: 100nF 50V X7R; C0603; LCSC C14663
C2: 10uF 25V X5R; C0805; LCSC C15850
J1: KF128-5.08-3P; CONN-TH_3P-P5.08_KF128-5.08-3P; LCSC C474953
J2, J3: KF128-5.08-2P; CONN-TH_P5.08_KF128-5.08-2P; LCSC C474952
R1: 1.27k 0.1% 25ppm; R0603; LCSC C861195
R2: 121k 0.1% 25ppm; R0603; LCSC C861095
R3, R5: 10.0k 0.1% 25ppm; R0603; LCSC C95204
R4: 24.9k 0.1% 25ppm; R0603; LCSC C136967
U1: AD8226ARZ-R7; SOIC-8_L5.0-W4.0-P1.27-LS6.0-BL; LCSC C34250
U2: OPA2333AIDR; SOP-8_L4.9-W3.9-P1.27-LS6.0-BL; LCSC C38732

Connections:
+3V3: C1.1, C2.1, C3.1, J3.1, R2.1, U1.8 (+VS), U2.8 (V+)
/AMP1_OUT: U1.7 (VOUT), U2.5 (INB+)
/FB2: R4.2, R5.1, U2.6 (INB-)
/IN_N: J1.1, U1.1 (-IN)
/IN_P: J1.2, U1.4 (+IN)
/RG_A: R1.1, U1.2 (RG/2)
/RG_B: R1.2, U1.3 (RG)
/VOUT: J2.1, R4.1, U2.7 (OUTB)
/VREF: R5.2, U1.6 (REF), U2.1 (OUTA), U2.2 (INA-)
/VREF_SET: C4.1, R2.2, R3.1, U2.3 (INA+)
GND: C1.2, C2.2, C3.2, C4.2, J1.3, J2.2, J3.2, R3.2, U1.5 (-VS), U2.4 (V-)

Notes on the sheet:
SIGNAL CHAIN J1 -> U1 (G1 = 39.90) -> U2B (G2 = 3.49) -> J2
J1 POLE ORDER: IN- / IN+ / GND - the silk legend must read that way
IN+ still drives U1 pin 4; the polarity convention is unchanged (P6)
NO OUTPUT ISOLATION RESISTOR: OPA2333 Fig.15's mid-30 % overshoot into 1 nF is a UNITY-GAIN figure.
This stage runs at noise gain 3.49 - simulated 6.6 % into the 1 nF of Q8, ~63 deg phase margin.
Nothing needs isolating; block-only scope excludes conditioning anyway.
PEDESTAL R2/R3 off +3V3 = 0.2519 V, C4 on the DIVIDER node, U2A buffers it for U1 REF
AD8226's 2 ohm REF rule: met at DC and low frequency (B9: 0.43 mohm DC, 0.17 ohm at 60 Hz),
crossed above ~700 Hz - harmless, Q1's common mode is STATIC. Numbers in the box.
STAGE-2 GAIN SET R5 RETURNS TO /VREF, NOT GND - that is what makes the pedestal EXACT
POWER +3V3 arrives at J3; C2 10uF bulk at J3; C1/C3 100nF at pin 8 of U1/U2 (AD8226 Fig.61, OPA2333 p15)
bb-amp - BRIDGE FRONT END ON ONE 3.3 V RAIL (architecture/blocks.md) TRANSFER FUNCTION Vout = Vref + G1*G2*Vdiff G1*G2 = 139.2 V/V, Vref = 0.252 V Vout(-1 mV) = 0.113 V Vout(0) = 0.252 V Vout(+20 mV) = 3.037 V +25 mV overload clips at (V+) - 0.05 V and recovers, no fold-back. GAIN SPLIT G1 * G2 = 3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

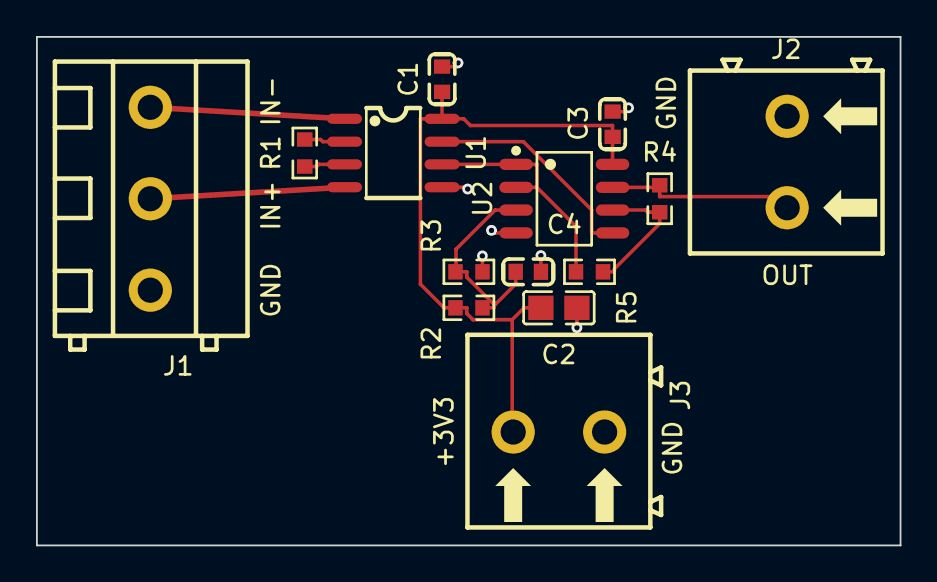
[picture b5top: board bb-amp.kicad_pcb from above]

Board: 2 copper layers, 48.0 x 28.3 mm, 14 parts (0 on the bottom side), 11 nets.

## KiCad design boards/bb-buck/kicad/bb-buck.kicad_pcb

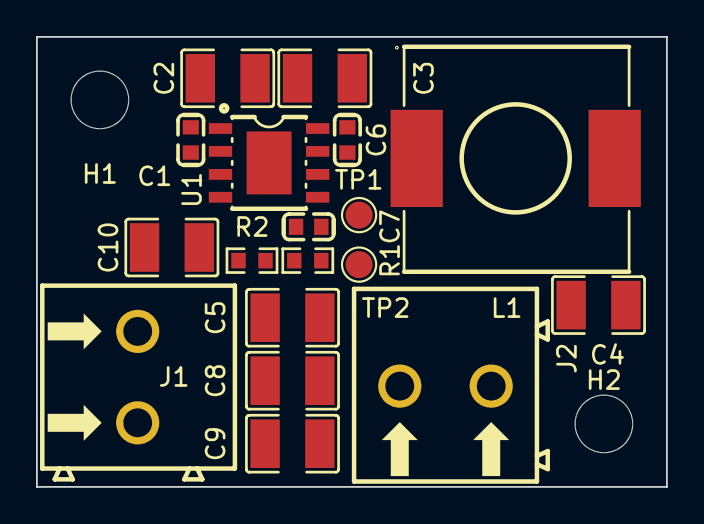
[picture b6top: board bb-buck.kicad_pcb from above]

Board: 2 copper layers, 35.0 x 25.0 mm, 20 parts (0 on the bottom side), 7 nets, no tracks yet.

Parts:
C1: 220nF 50V X7R; C0603
C2, C3, C10: 10uF 50V X7R; C1210
C4, C5, C8, C9: 22uF 25V X7R; C1210
C6: 100nF 50V X7R; C0603
C7: 1uF 25V X7R; C0603
H1, H2: M3_3.2mm; MountingHole_3.2mm_M3
J1, J2: KF128-5.08-2P; CONN-TH_P5.08_KF128-5.08-2P
L1: 15uH; IND-SMD_L12.5-W12.5_RLF12545T
R1: 102k 0.1% 25ppm; R0603
R2: 25.5k 0.1% 25ppm; R0603
TP1: SW; TestPoint_Pad_D1.5mm
TP2: GND; TestPoint_Pad_D1.5mm
U1: LMR33630ADDAR; ESOP-8_L4.9-W3.9-P1.27-LS6.0-TL-EP

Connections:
+5V: C4.1, C5.1, C8.1, C9.1, J2.1, L1.2, R1.1
+VIN: C1.1, C2.1, C3.1, C10.1, J1.1, U1.2, U1.3
/BST: C6.1, U1.7
/FB: R1.2, R2.1, U1.5
/SW: C6.2, L1.1, TP1.1, U1.8
/VCC: C7.1, U1.6
GND: C1.2, C2.2, C3.2, C4.2, C5.2, C7.2, C8.2, C9.2, C10.2, J1.2, J2.2, R2.2, TP2.1, U1.1, U1.9
